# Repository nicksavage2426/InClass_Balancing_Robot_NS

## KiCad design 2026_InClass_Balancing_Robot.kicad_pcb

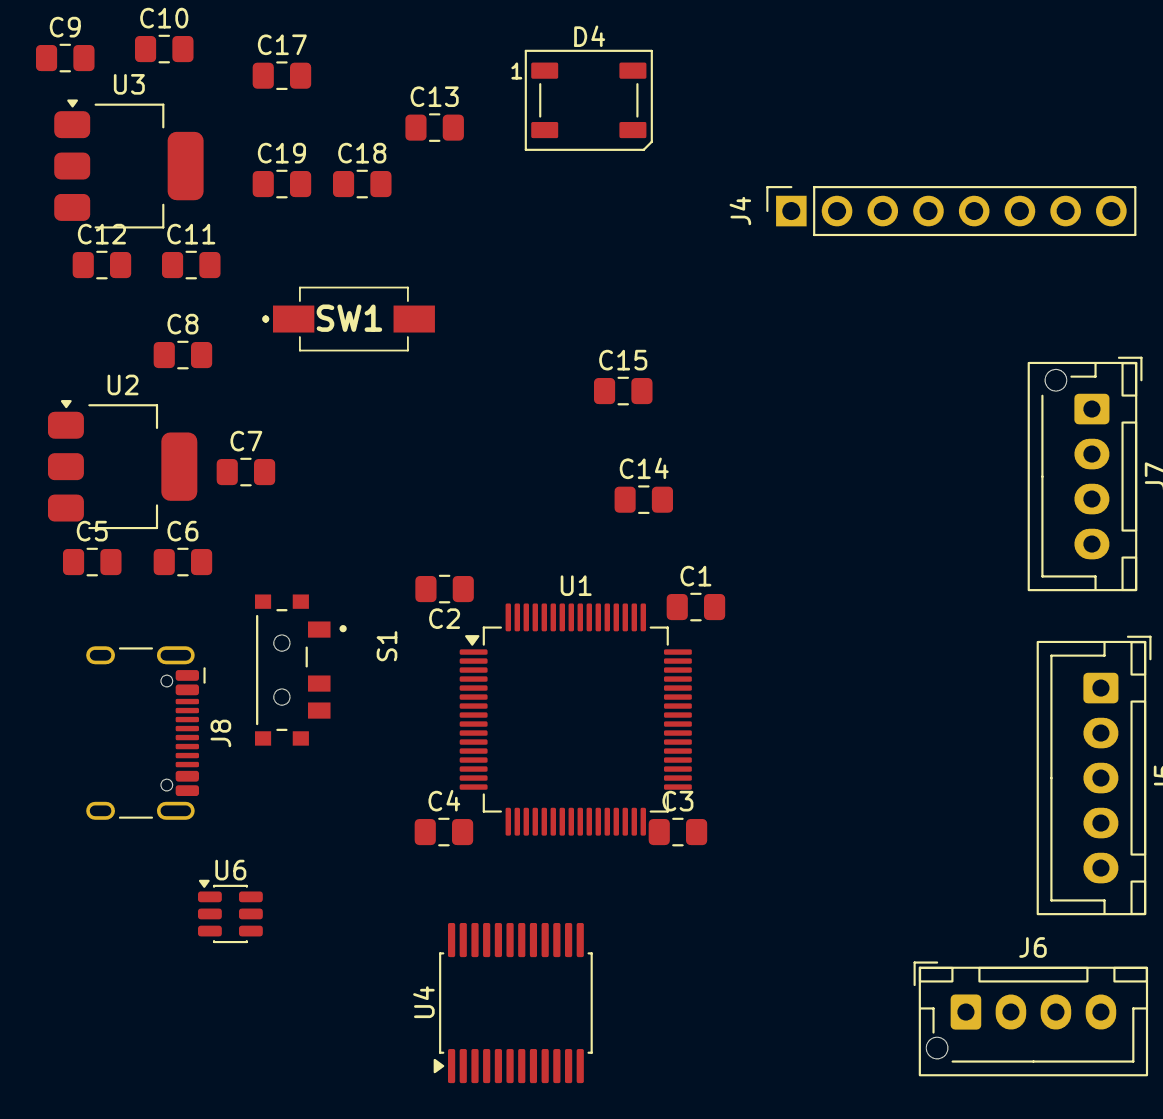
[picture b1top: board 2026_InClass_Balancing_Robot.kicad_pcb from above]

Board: 2 copper layers, 31 parts (0 on the bottom side), 33 nets, no tracks yet.

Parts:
C1, C2, C3, C5, C7, C9, C11, C13, C14, C15, C17: 0.1uF; C_0805_2012Metric_Pad1.18x1.45mm_HandSolder
C4, C6, C8, C10, C12: 10uF; C_0805_2012Metric_Pad1.18x1.45mm_HandSolder
C18: 2.2uF; C_0805_2012Metric_Pad1.18x1.45mm_HandSolder
C19: 0.01uF; C_0805_2012Metric_Pad1.18x1.45mm_HandSolder
D4: WS2812B; LED_WS2812B_PLCC4_5.0x5.0mm_P3.2mm
J4: CONN_MPU6050; PinSocket_1x08_P2.54mm_Vertical
J5: MT6701_CONN; JST_XH_B5B-XH-A_1x05_P2.50mm_Vertical
J6: ENCODER_CONN; JST_XH_B4B-XH-AM_1x04_P2.50mm_Vertical
J7: Conn_01x04; JST_XH_B4B-XH-AM_1x04_P2.50mm_Vertical
J8: USB_C_Receptacle; USB_C_Receptacle_HCTL_HC-TYPE-C-16P-01A
S1: RST_SWITCH; SW_SLW-66527511-SMT-TR
SW1: SW_uP_Reset
U1: STM32F401RBTx; LQFP-64_10x10mm_P0.5mm
U2, U3: LD1117S50TR_SOT223; SOT-223-3_TabPin2
U4: TB6612FNG; SSOP-24_5.3x8.2mm_P0.65mm
U6: USBLC6-2SC6; SOT-23-6

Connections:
5V_REG: C7.1, C8.1, U2.2 (VO)
+3.3V: C1.1, C2.1, C3.1, C4.1, C11.1, C12.1, C14.1, C17.1, J5.1, J6.1, J7.1, S1.3, U1.13 (VREF+), U1.19 (VDD), U1.32 (VDD), U1.48 (VDD), U1.64 (VDD), U3.2 (VO), U4.20 (VCC)
+5V: C9.1, C10.1, C13.1, D4.1 (VDD), J4.1, U3.3 (VI)
/ENC_A: J6.2, U1.59 (PB7)
/ENC_B: J6.3, U1.58 (PB6)
/IMU_INT: J4.8, U1.2 (PC13)
/IMU_SCL: J4.3, U1.61 (PB8)
/IMU_SDA: J4.4, U1.62 (PB9)
/MD_A01: U4.1 (AO1), U4.2 (AO1)
/MD_A02: U4.5 (AO2), U4.6 (AO2)
/MD_AIN1: U1.17 (PA3), U4.21 (AIN1)
/MD_AIN2: U1.16 (PA2), U4.22 (AIN2)
/MD_B01: U4.11 (BO1), U4.12 (BO1)
/MD_B02: U4.7 (BO2), U4.8 (BO2)
/MD_BIN1: U1.22 (PA6), U4.17 (BIN1)
/MD_BIN2: U1.23 (PA7), U4.16 (BIN2)
/MD_PWMA: U1.15 (PA1), U4.23 (PWMA)
/MD_PWMB: U1.21 (PA5), U4.15 (PWMB)
/MD_STBY: U1.20 (PA4), U4.19 (STBY)
/MT_PWM: J5.3, U1.37 (PC6)
/MT_SCL: J5.4, U1.41 (PA8)
/MT_SDA: J5.5, U1.40 (PC9)
/SWCLK: J7.2, U1.49 (PA14)
/SWDIO: J7.4, U1.46 (PA13)
/WS_DIN: D4.4 (DIN), U1.14 (PA0)
GND: C1.2, C2.2, C3.2, C4.2, C5.2, C6.2, C7.2, C8.2, C9.2, C10.2, C11.2, C12.2, C13.2, C14.2, C15.2, C17.2, C18.2, C19.2, D4.3 (VSS), J4.2, J5.2, J6.4, J7.3, J8.A1 (GND), J8.A12 (GND), J8.B1 (GND), J8.B12 (GND), J8.S1 (SHIELD), S1.1, SW1.1 (A), U1.12 (VSSA), U1.18 (VSS), U1.28 (PB2), U1.31 (VSS), U1.47 (VSS), U1.63 (VSS), U2.1 (GND), U3.1 (GND), U4.3 (PGND1), U4.4 (PGND1), U4.9 (PGND2), U4.10 (PGND2), U4.18 (GND), U6.2 (GND)
unnamed: J8.A6 (D+), J8.B6 (D+), U6.3 (I/O2)
unnamed: J8.A7 (D-), J8.B7 (D-), U6.1 (I/O1)
unnamed: J8.A4 (VBUS), J8.A9 (VBUS), J8.B4 (VBUS), J8.B9 (VBUS)
unnamed: C19.1, SW1.2 (B), U1.7 (NRST)
unnamed: C18.1, U1.30 (VCAP1)
unnamed: C15.1, U4.13 (VM2), U4.14 (VM3), U4.24 (VM1)
VM: C5.1, C6.1, U2.3 (VI)

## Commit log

2026-04-30 all files in project
    layout from class
